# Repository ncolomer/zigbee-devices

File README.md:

# Zigbee Devices

DIY Zigbee firmware projects for the [Seeed Studio XIAO ESP32C6](https://wiki.seeedstudio.com/xiao_esp32c6_zigbee_arduino/), built with PlatformIO and the Arduino 3 framework. All devices join a [Zigbee2MQTT](https://www.zigbee2mqtt.io/) network.

## Projects

| Project | Description | Latest release |
|---|---|---|
| `garage-console` | 16-input switch console (Zigbee toggle/on-off sources) |  |
| `garage-doors` | 4-relay switch controller for garage and yard doors/gates |  |
| `garage-water` | Rain/grid water source selector + dual water meter |  |
| `garage-water-tank` | Ultrasonic water tank level monitor (OLED + Zigbee) |  |
| `water-meter` | Battery-powered pulse counter for mechanical water meters |  |

## Hardware

- **Board**: Seeed Studio XIAO ESP32C6
- **Build tool**: PlatformIO
- **Platform**: [pioarduino/platform-espressif32](https://github.com/pioarduino/platform-espressif32)

## Build

```bash
pio run -e debug    # debug build
pio run -e release  # release build
pio run --target upload  # flash firmware
```

## Release

Each firmware is released on its own, by pushing a `<project>-v<MAJOR.MINOR.PATCH>` tag:

```bash
git tag garage-doors-v0.1.2 && git push origin garage-doors-v0.1.2
```

[`release.yml`](.github/workflows/release.yml) builds the `release` env with that version and publishes a GitHub release with
the application image, the full flash image (`.factory.bin`), the Zigbee2MQTT external converter and, for OTA-enabled firmwares,
the Zigbee OTA image (`.ota`).
Local builds are versioned `0.0.0` unless `FIRMWARE_VERSION` is set.

Each release also refreshes the rolling `ota-index` release: its `index.json` lists the latest `.ota` of every firmware, for
Zigbee2MQTT's `ota.zigbee_ota_override_index_location`.

Firmwares opt into OTA with `custom_ota_manufacturer` and `custom_ota_image_type` (unique per firmware) in `platformio.ini`: the
firmware gets them as defines ([`scripts/firmware_version.py`](scripts/firmware_version.py)), and the workflow wraps the build into a
`.ota` with Espressif's [`image_builder_tool.py`](https://github.com/espressif/esp-zigbee-sdk/tree/master/tools/image_builder_tool).

## Structure

Each project follows this layout:

```
project/
├── platformio.ini
├── src/main.cpp
└── z2m-external-converter/   # Zigbee2MQTT external converter (if needed)
```

## Libraries

Shared code lives in `libraries/` and is referenced by projects via `lib_extra_dirs`.

## Serial Monitor

```zsh
espmon() { local p=$1 b=${2:-115200}; while :; do [[ -e $p ]] && { stty -f "$p" "$b" raw && cat "$p"; } || sleep .1; done }
espmon /dev/cu.usbmodem1101
```

Reconnects automatically when the device is unplugged/replugged.

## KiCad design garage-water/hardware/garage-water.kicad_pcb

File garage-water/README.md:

# Garage Water

Mains-powered Zigbee **router** for a garage water console. Drop-in replacement for a
ptvo.info `garage.water` firmware, reimplemented on a Seeed XIAO ESP32-C6 with a Grove
Shield. It selects the water source with a relay and totals two water meters.

## Hardware

- **Board**: Seeed Studio XIAO ESP32C6 + Grove Shield for XIAO
- **Power**: mains via USB-C (no battery) — always awake, no deep sleep
- **Relay**: 3.3V-piloted, Normally Open, **energized on LOW**

### Pin Connections

| Function            | Pin  | GPIO   | Notes                                              |
|---------------------|------|--------|----------------------------------------------------|
| Relay control       | D4   | 22     | ON/tank = HIGH (de-energized), OFF/grid = LOW      |
| Water meter 1 pulse | D1   | 1      | internal pull-up, FALLING interrupt, 10 ms debounce|
| Water meter 2 pulse | D2   | 2      | internal pull-up, FALLING interrupt, 10 ms debounce|
| Factory reset       | BOOT | 9      | onboard button, hold 3 s                           |
| Status LED          | —    | 15     | pairing / activity feedback                        |
| Spare               | D0, D7 | 0, 17 | unused                                            |

**Water source / fail-safe:** the relay idles HIGH (de-energized) via pull-up, and the
tank is wired to the de-energized side, so an **unpowered device selects the rain tank**.
Selecting grid (`OFF`) energizes the coil. Relay state is remembered across power loss.

## Behavior

- **Relay (EP1)**: Z2M on/off toggles the water source. `ON` = rain tank, `OFF` = grid.
  State persists to NVS and is restored (driven to the GPIO) on boot; a fresh device
  defaults to tank.
- **Water meters (EP2, EP3)**: each pulse adds `liters_per_pulse` to that meter's
  cumulative volume and reports it over the SE Metering cluster (`currentSummDelivered`).
- **Factory reset**: hold BOOT ≥ 3 s to leave the Zigbee network and re-pair. Meter
  totals and relay state (NVS) are preserved; a full wipe is `pio run --target erase`.

## Configuration

All configuration is done over Zigbee2MQTT after pairing:

| Entity                     | Description                                | Default |
|----------------------------|--------------------------------------------|---------|
| `state_relay`              | Water source (ON = tank, OFF = grid)       | tank    |
| `water_volume_meter1/2`    | Cumulative volume (m³, writable to calibrate) | 0    |
| `liters_per_pulse_meter1/2`| Liters per pulse (1–1000)                  | 10      |

## Storage (NVS)

- Relay state saved on every change.
- Each meter reading saved every 1000 L (1 m³) change, and immediately on a remote
  calibration write.

## Zigbee2MQTT

External converter in `z2m-external-converter/garage-water.mjs`:

1. Copy to `data/external_converters/`
2. Add to `configuration.yaml`:
   ```yaml
   external_converters:
     - garage-water.mjs
   ```
3. Restart Zigbee2MQTT

## Router mode

This firmware runs as a Zigbee **router** (`ZIGBEE_MODE_ZCZR`, `zigbee_zczr.csv`
partitions). Being permanently powered, it repeats the mesh and can parent other end
devices.

## OTA

Not implemented yet. The `zigbee_zczr.csv` partition scheme already provides the dual
OTA app slots, so OTA can be added later without repartitioning.

## Libraries

- `ZigbeeRelaySwitch` — genOnOff relay endpoint (toggle mode, NVS-persisted state)
- `ZigbeeWaterMeter` — SE Metering endpoint with custom `liters_per_pulse` attribute
- `StatusLed` — async LED blink via FreeRTOS task
- `Debug` — conditional serial logging (debug builds only)

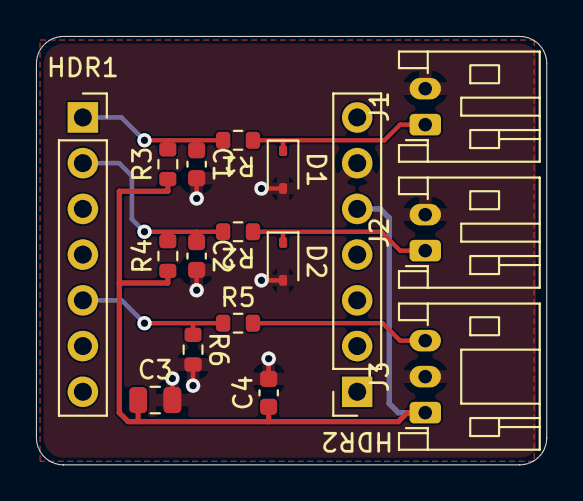
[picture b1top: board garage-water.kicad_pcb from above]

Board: 2 copper layers, 28.4 x 23.8 mm, 17 parts (0 on the bottom side), 8 nets.

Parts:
C1, C2, C4: 100nF; C_0603_1608Metric
C3: 10uF; C_0805_2012Metric
D1, D2: ESD 3.3V; D_SOD-323
HDR1, HDR2: Header_1x7_2.54mm; PinSocket_1x07_P2.54mm_Vertical
J1: METER1; JST_PH_S2B-PH-K_1x02_P2.00mm_Horizontal
J2: METER2; JST_PH_S2B-PH-K_1x02_P2.00mm_Horizontal
J3: RELAY; JST_PH_S3B-PH-K_1x03_P2.00mm_Horizontal
R1, R2: 1k; R_0603_1608Metric
R3, R4, R6: 10k; R_0603_1608Metric
R5: 330; R_0603_1608Metric

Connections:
/+3V3: C3.1, C4.1, HDR2.5, J3.1, R3.1, R4.1
/GND: C1.2, C2.2, C3.2, C4.2, D1.2, D2.2, HDR2.6, J1.2, J2.2, J3.2, R6.2
/M1_IN: D1.1, J1.1, R1.1
/M2_IN: D2.1, J2.1, R2.1
/METER1: C1.1, HDR1.1, R1.2, R3.2
/METER2: C2.1, HDR1.2, R2.2, R4.2
/RELAY_CMD: HDR1.5, R5.1, R6.1
/RELAY_IN: J3.3, R5.2

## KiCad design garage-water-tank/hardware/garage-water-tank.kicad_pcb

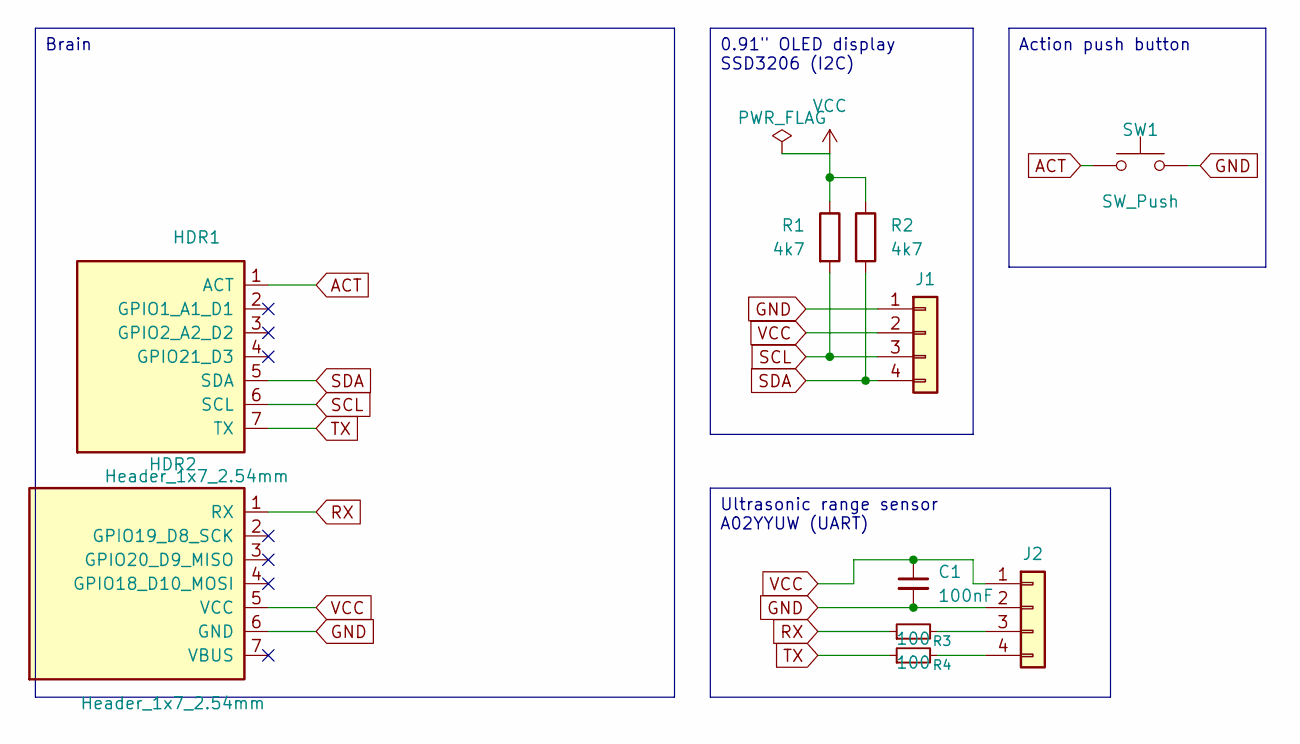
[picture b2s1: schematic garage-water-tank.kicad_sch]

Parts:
C1: 100nF; C_0805_2012Metric; LCSC C49678
HDR1, HDR2: Header_1x7_2.54mm; PinSocket_1x07_P2.54mm_Vertical; LCSC C22438157
J1: Conn_01x04; PinSocket_1x04_P2.54mm_Vertical_SMD_low_profile_Pin1Left; MPN HX PM2.54-1x4P TP-YQ; LCSC C42379197
J2: Conn_01x04; JST_PH_B4B-PH-K_1x04_P2.00mm_Vertical; MPN B4B-PH-K-S(LF)(SN); LCSC C131334
R1, R2: 4k7; R_0805_2012Metric; LCSC C17673
R3, R4: 100; R_0805_2012Metric; LCSC C17408
SW1: SW_Push; SW_PUSH_6mm_H13mm

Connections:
ACT: HDR1.1 (ACT), SW1.1
GND: C1.2, HDR2.6 (GND), J1.1, J2.2, SW1.2
unnamed: J2.3, R3.2
unnamed: J2.4, R4.2
RX: HDR2.1 (RX), R3.1
SCL: HDR1.6 (SCL), J1.3, R1.2
SDA: HDR1.5 (SDA), J1.4, R2.2
TX: HDR1.7 (TX), R4.1
VCC: C1.1, HDR2.5 (VCC), J1.2, J2.1, R1.1, R2.1

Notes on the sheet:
0.91" OLED display SSD3206 (I2C)
Ultrasonic range sensor A02YYUW (UART)
Action push button
Brain

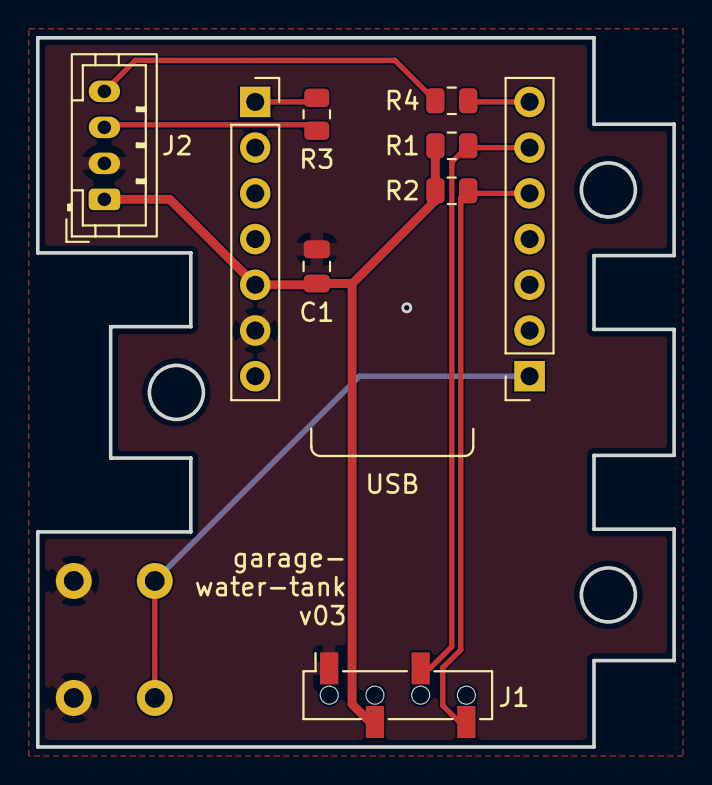
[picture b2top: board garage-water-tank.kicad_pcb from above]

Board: 2 copper layers, 35.3 x 39.4 mm, 10 parts (1 on the bottom side), 9 nets.

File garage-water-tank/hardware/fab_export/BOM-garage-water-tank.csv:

"Designator","Comment","Footprint","LCSC Part #"
"C1","100nF","Capacitor_SMD:C_0805_2012Metric","C49678"
"HDR1,HDR2","Header_1x7_2.54mm","Connector_PinSocket_2.54mm:PinSocket_1x07_P2.54mm_Vertical","C22438157"
"J1","Conn_01x04","garage-water-tank:PinSocket_1x04_P2.54mm_Vertical_SMD_low_profile_Pin1Left","C42379197"
"J2","Conn_01x04","Connector_JST:JST_PH_B4B-PH-K_1x04_P2.00mm_Vertical","C131334"
"R1,R2","4k7","Resistor_SMD:R_0805_2012Metric","C17673"
"R3,R4","100","Resistor_SMD:R_0805_2012Metric","C17408"

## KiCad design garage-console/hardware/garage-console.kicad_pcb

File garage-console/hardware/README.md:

# garage-console — hardware

16-channel switch input carrier board for a Seeed Studio XIAO ESP32C6.

Each of the 16 JST XH connectors carries GND plus one dedicated input, so a
momentary or toggle switch can be wired to it with a 2-wire cable. The ESP32C6
does not have 16 spare GPIOs, so the inputs land on an I²C port expander and the
expander raises an interrupt line when any of them changes.

Layout is modelled on the [Grove Shield for Seeeduino XIAO](https://wiki.seeedstudio.com/Grove-Shield-for-Seeeduino-XIAO-embedded-battery-management-chip/)
— a XIAO carrier with connectors broken out — minus the battery management, since
this board is permanently powered from the XIAO's USB-C.

## Design decisions

**PCF8575 rather than MCP23017.** The MCP23017 was the first choice, but its
GPA7 and GPB7 pins are output-only ([datasheet DS20001952D](https://ww1.microchip.com/downloads/en/DeviceDoc/20001952C.pdf),
pin table p.11), leaving only 14 usable inputs for 16 switches. The PCF8575 has
16 true quasi-bidirectional I/Os plus an open-drain interrupt output, so all 16
channels stay uniform. No local copy of the MCP23017 datasheet is kept — it's
a rejected alternative, not a part this design uses.

**No external pull-ups on the inputs.** The PCF8575 sources IOH = 30–300 µA to
VCC on any pin written high, which is the input configuration ([PCF8575 SCPS121I](datasheets/PCF8575-TI-datasheet.pdf)
§8.3). One 100 nF cap per input filters EMI picked up on the switch cabling and
debounces the contact in hardware. The trade-off is a slow release edge —
100 nF / 30 µA ≈ 8 ms worst case — which is harmless for switches and is why no
external pull-ups are fitted.

**Powered from the XIAO's USB-C.** +3V3 for the expander comes from the XIAO's
on-module LDO (module pin 12). Nothing on this board draws meaningful current
(PCF8575 standby is 10 µA max), so there is no regulator, no battery, and no
charger. No power indicator either — the XIAO's own `LED_BUILTIN` serves that
purpose, so the board carries no LED of its own.

## Files

| Path | Contents |
|---|---|
| `garage-console.kicad_pro` | KiCad project |
| `garage-console.kicad_sch` | Schematic (A3) |
| `garage-console.kicad_pcb` | Board layout |
| `datasheets/` | Local copies of every datasheet the design relies on |
| `3dmodels/` | Project-local STEP model(s) not available in any installed library |
| `garage_console.kicad_sym` | Project-local symbol library — `XIAO_HDR_A`/`XIAO_HDR_B`, the named-pin schematic symbols behind HDR1/HDR2 |
| `fab_export/` | Upload-ready production files, see Ordering |
| `jlcpcb-cpl-corrections.json` | Placement corrections applied to the CPL, see Ordering |

## Ordering

The three files in `fab_export/` are tracked, so the board can be ordered from
a clone without installing KiCad. On JLCPCB, upload:

| File | Where |
| --- | --- |
| `garage-console-gerbers.zip` | PCB order (Gerber) |
| `BOM-garage-console.csv` | Assembly → "BOM File" |
| `CPL-garage-console.csv` | Assembly → "CPL File" |

Economic PCBA, top side only, 2 layers. Economic supports through-hole, so the
JST connectors and both pin sockets are machine-placed along with the SMD parts;
nothing here needs hand-soldering. Everything on this board clears the Economic
limits comfortably — the tightest is U1's 0.65 mm pin pitch against a 0.4 mm
floor. Note the board is 21 mm wide, below Standard PCBA's 70 × 70 mm minimum,
so Economic is the only tier it fits.

To regenerate, pass the corrections file, or the placement corrections are lost:

```
export_manufacturing_package(
  fab_house="jlcpcb",
  jlcpcb_cpl_corrections_path=".../jlcpcb-cpl-corrections.json",
  ...)
```

**Always check JLCPCB's Component Placements preview before paying.** KiCad and
JLCPCB disagree about a package's zero-degree orientation, and Konnect's CPL
writes the KiCad footprint *anchor* into the `Mid X`/`Mid Y` columns instead of
the component midpoint ([Konnect #667](https://github.com/mixelpixx/Konnect/issues/667)),
which displaces anything anchored on pin 1. `jlcpcb-cpl-corrections.json`
compensates for both — rotations for the JSTs, U1 and the sockets, positions for
the JSTs and sockets — with every value verified in that preview. U1 needs no
position offset because the SSOP-24 anchor is already its centre. **Drop the
position offsets if #667 is fixed**, or they will double-correct.

Libraries: every footprint comes from a stock KiCad library, so `fp-lib-table`
registers nothing project-scope and is empty. The only project-local library is
`garage_console.kicad_sym`, registered in `sym-lib-table` under the
`garage_console` nickname. Nothing on the board comes from the
[Seeed OPL KiCad library](https://github.com/Seeed-Studio/OPL_Kicad_Library)
any more — it was only ever needed for the XIAO module's footprint, which this
design dropped (see Layout), so its entry was removed rather than left pointing
at a machine-specific absolute path that wouldn't resolve on anyone else's
clone. An empty `garage_console.pretty/` was dropped for the same reason: git
doesn't track empty directories, so registering one only guarantees a
missing-library path on a fresh clone. Re-add both the directory and its
`fp-lib-table` entry if a project-local footprint is ever needed.

## Switch channel map

`SWn` is pulled low while the switch on `Jn` is closed.

| Connector | Net | PCF8575 pin | Port bit |
|---|---|---|---|
| J1 | SW1 | 4 (P00) | port 0, bit 0 |
| J2 | SW2 | 5 (P01) | port 0, bit 1 |
| J3 | SW3 | 6 (P02) | port 0, bit 2 |
| J4 | SW4 | 7 (P03) | port 0, bit 3 |
| J5 | SW5 | 8 (P04) | port 0, bit 4 |
| J6 | SW6 | 9 (P05) | port 0, bit 5 |
| J7 | SW7 | 10 (P06) | port 0, bit 6 |
| J8 | SW8 | 11 (P07) | port 0, bit 7 |
| J9 | SW9 | 13 (P10) | port 1, bit 0 |
| J10 | SW10 | 14 (P11) | port 1, bit 1 |
| J11 | SW11 | 15 (P12) | port 1, bit 2 |
| J12 | SW12 | 16 (P13) | port 1, bit 3 |
| J13 | SW13 | 17 (P14) | port 1, bit 4 |
| J14 | SW14 | 18 (P15) | port 1, bit 5 |
| J15 | SW15 | 19 (P16) | port 1, bit 6 |
| J16 | SW16 | 20 (P17) | port 1, bit 7 |

Every connector's pin 2 is GND.

## XIAO interface

| XIAO pin | Signal | GPIO | Notes |
|---|---|---|---|
| 3 (D2) | PCF_INT | GPIO2 | active-low, open-drain, 10 k pull-up (R3) |
| 5 (D4) | SDA | GPIO22 | 4.7 k pull-up (R1) |
| 6 (D5) | SCL | GPIO23 | 4.7 k pull-up (R2) |
| 12 | +3V3 | — | board supply, from the XIAO LDO |
| 13 | GND | — | |

D0, D1, D3, D6–D10 and VBUS are unconnected — the expander covers all 16
channels, so no direct GPIOs are needed.

## Firmware notes

I²C address is **0x20** (7-bit): A2:A1:A0 are tied to GND, and the PCF8575
address is `0100 A2 A1 A0` (SCPS121I §8.3.3).

The part has no configuration or status registers. Writing `0xFFFF` once *is*
the input configuration; after that, reads return the pin states.

```cpp
Wire.begin(22, 23);                  // SDA=GPIO22 (D4), SCL=GPIO23 (D5)

Wire.beginTransmission(0x20);        // all 16 pins to input (weak pull-up on)
Wire.write(0xFF); Wire.write(0xFF);
Wire.endTransmission();

pinMode(2, INPUT);                   // R3 already pulls PCF_INT up
attachInterrupt(2, onChange, FALLING);

// in the handler's deferred work:
Wire.requestFrom(0x20, 2);
uint8_t p0 = Wire.read();            // SW1..SW8,  bit 0 = SW1
uint8_t p1 = Wire.read();            // SW9..SW16, bit 0 = SW9
// bit low = switch closed; the read also clears INT
```

Reading the port is what clears INT, so the read must happen on every interrupt
or the line stays asserted. A change arriving during the ACK pulse can be lost
(SCPS121I §8.3.2) — poll once per second alongside the interrupt so a missed edge
self-corrects.

## BOM

| Ref | Qty | Value | Footprint | LCSC | Notes |
|---|---|---|---|---|---|
| U1 | 1 | PCF8575 | SSOP-24 0.65 mm | [C2863388](https://www.lcsc.com/product-detail/C2863388.html) | TI PCF8575DBR |
| HDR1, HDR2 | 2 | Socket, 1×7, 2.54 mm | `PinSocket_1x07_P2.54mm_Vertical` | [C22438157](https://www.lcsc.com/product-detail/C22438157.html) | hanxia HX PM2.54-1x7P ZC-Y, female, 8.5 mm socket height; carry the XIAO module's real electrical connections, see Layout |
| J1–J16 | 16 | JST XH 2-pin | B2B-XH-A vertical, 2.5 mm | [C158012](https://www.lcsc.com/product-detail/C158012.html) | cable side: XHP-2 housing + SXH-001T-P0.6 crimps |
| C1 | 1 | 100 nF X7R | 0805 | [C49678](https://www.lcsc.com/product-detail/C49678.html) | U1 decoupling |
| C2 | 1 | 10 µF X5R | 0805 | [C15850](https://www.lcsc.com/product-detail/C15850.html) | +3V3 bulk, next to the module's supply pin (HDR2) |
| C3–C18 | 16 | 100 nF X7R | 0805 | [C49678](https://www.lcsc.com/product-detail/C49678.html) | input filter, one per channel |
| R1, R2 | 2 | 4.7 kΩ | 0805 | [C17673](https://www.lcsc.com/product-detail/C17673.html) | I²C pull-ups (the XIAO has none) |
| R3 | 1 | 10 kΩ | 0805 | [C17414](https://www.lcsc.com/product-detail/C17414.html) | PCF_INT pull-up |

**The Seeed Studio XIAO ESP32C6 module itself is not in this BOM or schematic at all** — it
carries no copper on this board (see Layout) and its own pinout isn't formally
documented anywhere in this design beyond HDR1/HDR2's own pin names, so it's
easy to read the BOM and schematic and not realize a module is needed at all.
It must be sourced separately (Seeed 113991054), and its own DIP-14
through-holes need a set of male 2.54 mm pins soldered in by hand — these
plug into HDR1/HDR2's sockets, which is how the module is mounted.

No mounting holes — this board lives inside an enclosure that doesn't need them.

All passive LCSC numbers are JLCPCB Basic-library parts (no Extended-part assembly fee), picked for highest stock among matching value/footprint/tolerance. U1, J1–J16, and HDR1/HDR2 have no Basic-library equivalent — this specific I/O expander, the JST connectors, and 2.54 mm pin sockets aren't stocked there — so each lists the highest-stock Extended part matching the MPN already in the schematic.

Every part above also carries its LCSC number as an `LCSC` field on the schematic symbol itself (not just this table), so it flows straight through KiCad's own BOM export and into `kicad-jlcpcb-tools`.

Fab target: JLCPCB, 2 layer, 0.2 mm minimum trace and clearance. All passives are
0805 — easier to hand-solder/rework than 0402, at the cost of a slightly larger
board.

## Layout

The board is a 169.3 × 21.2 mm horizontal strip (trimmed to the connectors'
and module's actual extents — no unused margin, since there are no mounting
holes to clear). The top and bottom edges are colinear with the module's real
body (its footprint's `F.Courtyard`/`F.Fab` outline, back when it still had a
dedicated footprint — not the USB-C connector's silkscreen mark, which is
meant to hang off the edge — see below), not just "close to it". The left and
right edges are mirrored around the connector block's own centerline
(x = 93.15 mm) rather than the board's raw geometric center, which an earlier
revision's asymmetric width trim had drifted 0.75 mm away from. The 16 JST
connectors form two rows of 8 (one row per board edge), split into two
4-connector blocks per row with U1/HDR1/HDR2 sitting in the gap between the
blocks, centered both horizontally and vertically. The module's ceramic
antenna faces the top edge (right at the board edge — see antenna clearance
note below), USB-C faces the bottom edge. Each filter cap (C3–C18) is rotated
90° from a naive placement so its short axis (1.25 mm) faces the tight
left-right direction between connector columns, trading it for the board's
more plentiful vertical room.

**Filter caps are genuinely mirror-symmetric block-to-block.** Every JST
footprint (rotation 0° in both blocks) extends 5.475 mm to its own right and
only 2.975 mm to its left — an asymmetry baked into the footprint itself that
doesn't flip between blocks, so a true mirror needs an *asymmetric* offset
magnitude, not just an opposite sign. Left-block caps (C3–C10) sit at
`connector_x + 7.75 mm` (the connector's long side, verified clear of its
own courtyard with margin); most right-block caps (C12–C14, C16–C18) sit at
`connector_x − 5.3 mm` — the connector's short side, which needs less
clearance than the long side does. **C11 and C15 are the two exceptions**:
both sit at `connector_x + 7.805 mm`, on the same side as the left-block
caps rather than mirrored, because the mirrored position would put them
inside the R1–R3 group's courtyards (R1–R3 are fixed, off-limits to move).

**The XIAO module has no schematic symbol and no PCB footprint at all.** Its
real electrical connections are carried entirely by two standard 1×7,
2.54 mm female sockets, HDR1 and HDR2 — one per physical pin column of the
module's DIP-14 footprint (HDR1: GPIO0/GPIO1/PCF_INT/GPIO21/SDA/SCL/GPIO16;
HDR2: GPIO17/GPIO19/GPIO20/GPIO18/+3V3/GND/VBUS), each with correctly-named
pins in the schematic. HDR1/HDR2 are soldered flat onto this board; the
module's own male pins (soldered into its DIP-14 holes by hand, off-board —
not a part in this BOM) plug into the sockets, physically elevating the
module above the board surface by the socket height so it clears U1 and C1
underneath without touching them. This keeps every component on one side of
the board, which JLCPCB only charges a single assembly fee for (a 2-sided
assembly would double that fee for the sake of two parts). With no PCB
footprint for the module at all, there's nothing for the `courtyards_overlap`
DRC check to compare against U1/C1's courtyards in the first place.

An earlier revision instead gave the module its own dedicated PCB footprint
— zero pads, no courtyard, existing purely to hold the 3D model — while
keeping its schematic symbol fully wired for documentation. That worked, but
KiCad's schematic-parity check expects every schematic pin to find a
correspondingly-numbered footprint pad, and a zero-pad footprint can never
satisfy that: it produced a structural, permanent warning for all 14 pins
("no pad found for pin N in schematic"), one that could only be silenced
with a DRC exclusion, not actually resolved. Since 3D models are attached to
footprints and never inspected by DRC/ERC at all, the cleaner fix was to drop
that placeholder symbol/footprint entirely and instead give HDR1's own real,
already-connected footprint a *second*, independent 3D model entry — the
module's STEP file, positioned via its own offset/rotation so it renders in
the same physical spot as before. No symbol means no parity check to fail;
the module still renders correctly in the 3D viewer since a footprint (HDR1's)
is still there to carry it. The final transform is offset (13.73, −9.36,
8.8 mm), rotation (−90°, 0°, −90°).

**HDR1/HDR2's spacing was wrong for a while, and so was the transform above
until it was corrected alongside it.** An earlier revision placed HDR1 and
HDR2 16.4925 mm apart — the real, authoritative spacing (confirmed from
Seeed's own official OPL KiCad library footprint,
`Seeed Studio XIAO Series Library/XIAO-ESP32-C6-DIP.kicad_mod`, the same
library this project's schematic uses) is 15.24 mm, centered on x = 93.15 mm.
The footprint defines each pin twice — a real `thru_hole circle` pad and a
cosmetic `smd roundrect` annular pad 0.835 mm further out — and the original
extraction picked up the cosmetic pad for HDR2 and an incorrect average of
both pads for HDR1, instead of the real through-holes alone. Corrected
positions: HDR1 x = 100.77 (was 101.1875), HDR2 x = 85.53 (was 84.695), Y and
rotation unchanged for both. The module's 3D-model offset above is the
result *after* this correction — HDR1 moving −0.4175 mm required the same
shift in the model's offset.x to keep the module's world-space position
exactly where it had been visually confirmed correct. Re-verified with
`get_board_2d_view` (not `kicad-cli pcb render` — the two don't visually
agree closely enough for fine placement checks, confirmed directly): the
module now sits flush against both header columns with no gap on either
side. The one caveat on the model itself is unchanged: this second model is
a board-instance-local addition, not part of HDR1's stock library footprint
(`Connector_PinSocket_2.54mm:PinSocket_1x07_P2.54mm_Vertical`) — running
"Update Footprint from Library" on HDR1 would silently drop it.

Swapping the module's oversized, module-specific pads for HDR1/HDR2's small
standard socket pads also freed real copper/routing room in what was the
densest spot on the board — those oversized pads were a direct cause of
several clearance fights during autorouting in earlier revisions.

**Antenna clearance.** No keepout zone under the module's antenna end — with the
antenna now at the board's physical edge (copper on one side only, not
surrounding it) and the module elevated a few mm above the board surface on
the headers, the RF justification for a precautionary carve-out is much
weaker than when the module sat flush on the surface. Removed rather than
carried forward as unnecessary caution.

**Ground plane.** Both copper layers carry a full-board GND pour with a
*solid* pad connection (no thermal-relief spokes) rather than KiCad's default
thermal mode. The PCF8575's 0.65 mm pin pitch is too tight for the standard
2-spoke thermal relief — it kept failing DRC's `starved_thermal` check — and
solid fill also avoids the connectivity islands thermal relief can leave
behind on a densely-routed 2-layer board. The pour outline sits 0.2 mm inside
the board edge on all sides — JLCPCB's published minimum copper-to-routed-edge
clearance — rather than the tighter, sub-minimum inset an earlier revision
used. No dedicated GND stitching vias are needed — the 16 JST connectors'
and both header sockets' through-hole pins already bridge F.Cu and B.Cu
everywhere the dense signal routing would otherwise leave a pour region
isolated; each fill fragment on both layers was checked directly against
the via/pad list and every one lands on a real GND connection.

One `unconnected_items` DRC finding is left and is a known, checked-benign
zone-fill artifact, not a real gap: at the top-right corner (the rounded
corner's zone-inset vertex, board edge minus the 3 mm corner radius) DRC
reports `GND_top_solid` and `GND_bottom_solid` as unconnected. Direct
polygon inspection shows both layers' fill share the exact same points at
that vertex, and both zones tie into the same net through dozens of shared
GND pads elsewhere on the board — a stitching via added right at the flagged
point didn't change the finding (and cost real edge clearance), confirming
it's a KiCad connectivity-check quirk specific to that corner geometry, not
an electrical break. This has now shown up at the same relative corner
across more than one revision of this outline.

**Routing.** Autorouted with [Freerouting](https://github.com/freerouting/freerouting)
via its MCP server, driven from a Specctra DSN exported through KiCad's own
`pcbnew.ExportSpecctraDSN`/`ImportSpecctraSES` (the same mechanism as *File →
Export/Import → Specctra*, just scripted). The GND pours export as Specctra
`plane` records **as long as they exist at export time** — Freerouting then
treats GND as already satisfied by the plane and never draws an explicit GND
trace or via for it, so the 16 filter caps' GND legs, and everything else on
the net, rely purely on the pour (see Ground Plane above). This is
different from the antenna keepout (removed in this revision) and any other
rule-area keepout zone, which Freerouting treats as a hard routing obstacle
rather than just a copper-fill exclusion — a keepout can only exist once
routing is done, while a GND *pour* zone should stay in place through export
precisely so Freerouting reads it as a plane instead of routing GND as
ordinary traces.
A few of Freerouting's automatic-neckdown segments came back under the 0.2 mm
fab minimum and were widened by hand after import; a couple of vias needed
small nudges to clear adjacent copper. One or two connections per revision
have consistently been too tightly boxed in for Freerouting to close on its
own — U1's SW-net pins sit on a 0.65 mm pitch with GND/SDA/SCL fan-out
immediately around them, and different specific connections have hit this
depending on the exact routing pass (this revision: `SW11` between C13 and
U1 pin 15, plus a trivial direct `+3V3` link between R1 and R2 that
Freerouting simply missed). Each SW-net case was solved with a small
grid-based pathfinder (clearance-aware, both copper layers, via cost
included) rather than by guesswork, since the pocket is tight enough that
hand-picked straight lines and even a first pathfinder pass (modeling only
trace clearance, not the larger clearance a via itself needs) reliably
landed on or too close to existing copper — the working version models via
placement with its own, stricter clearance check before committing to a
layer-switch point. Every change was re-verified with a fresh DRC pass.

**3D models.** J1–J16, U1, HDR1 and HDR2 use the standard `.step` models
bundled with their KiCad libraries. The OPL library's XIAO footprints have no
dedicated XIAO ESP32C6 model — only placeholder bodies for other XIAO
variants, gated behind a `${AMZPATH}` environment variable this machine
doesn't have configured — so `3dmodels/seeed-studio-xiao-esp32c6.step`
(copied from the `water-tank-monitor` project's assets) is used instead, via
a `${KIPRJMOD}`-relative path, attached as HDR1's second 3D model entry (see
Layout for why and the exact transform).

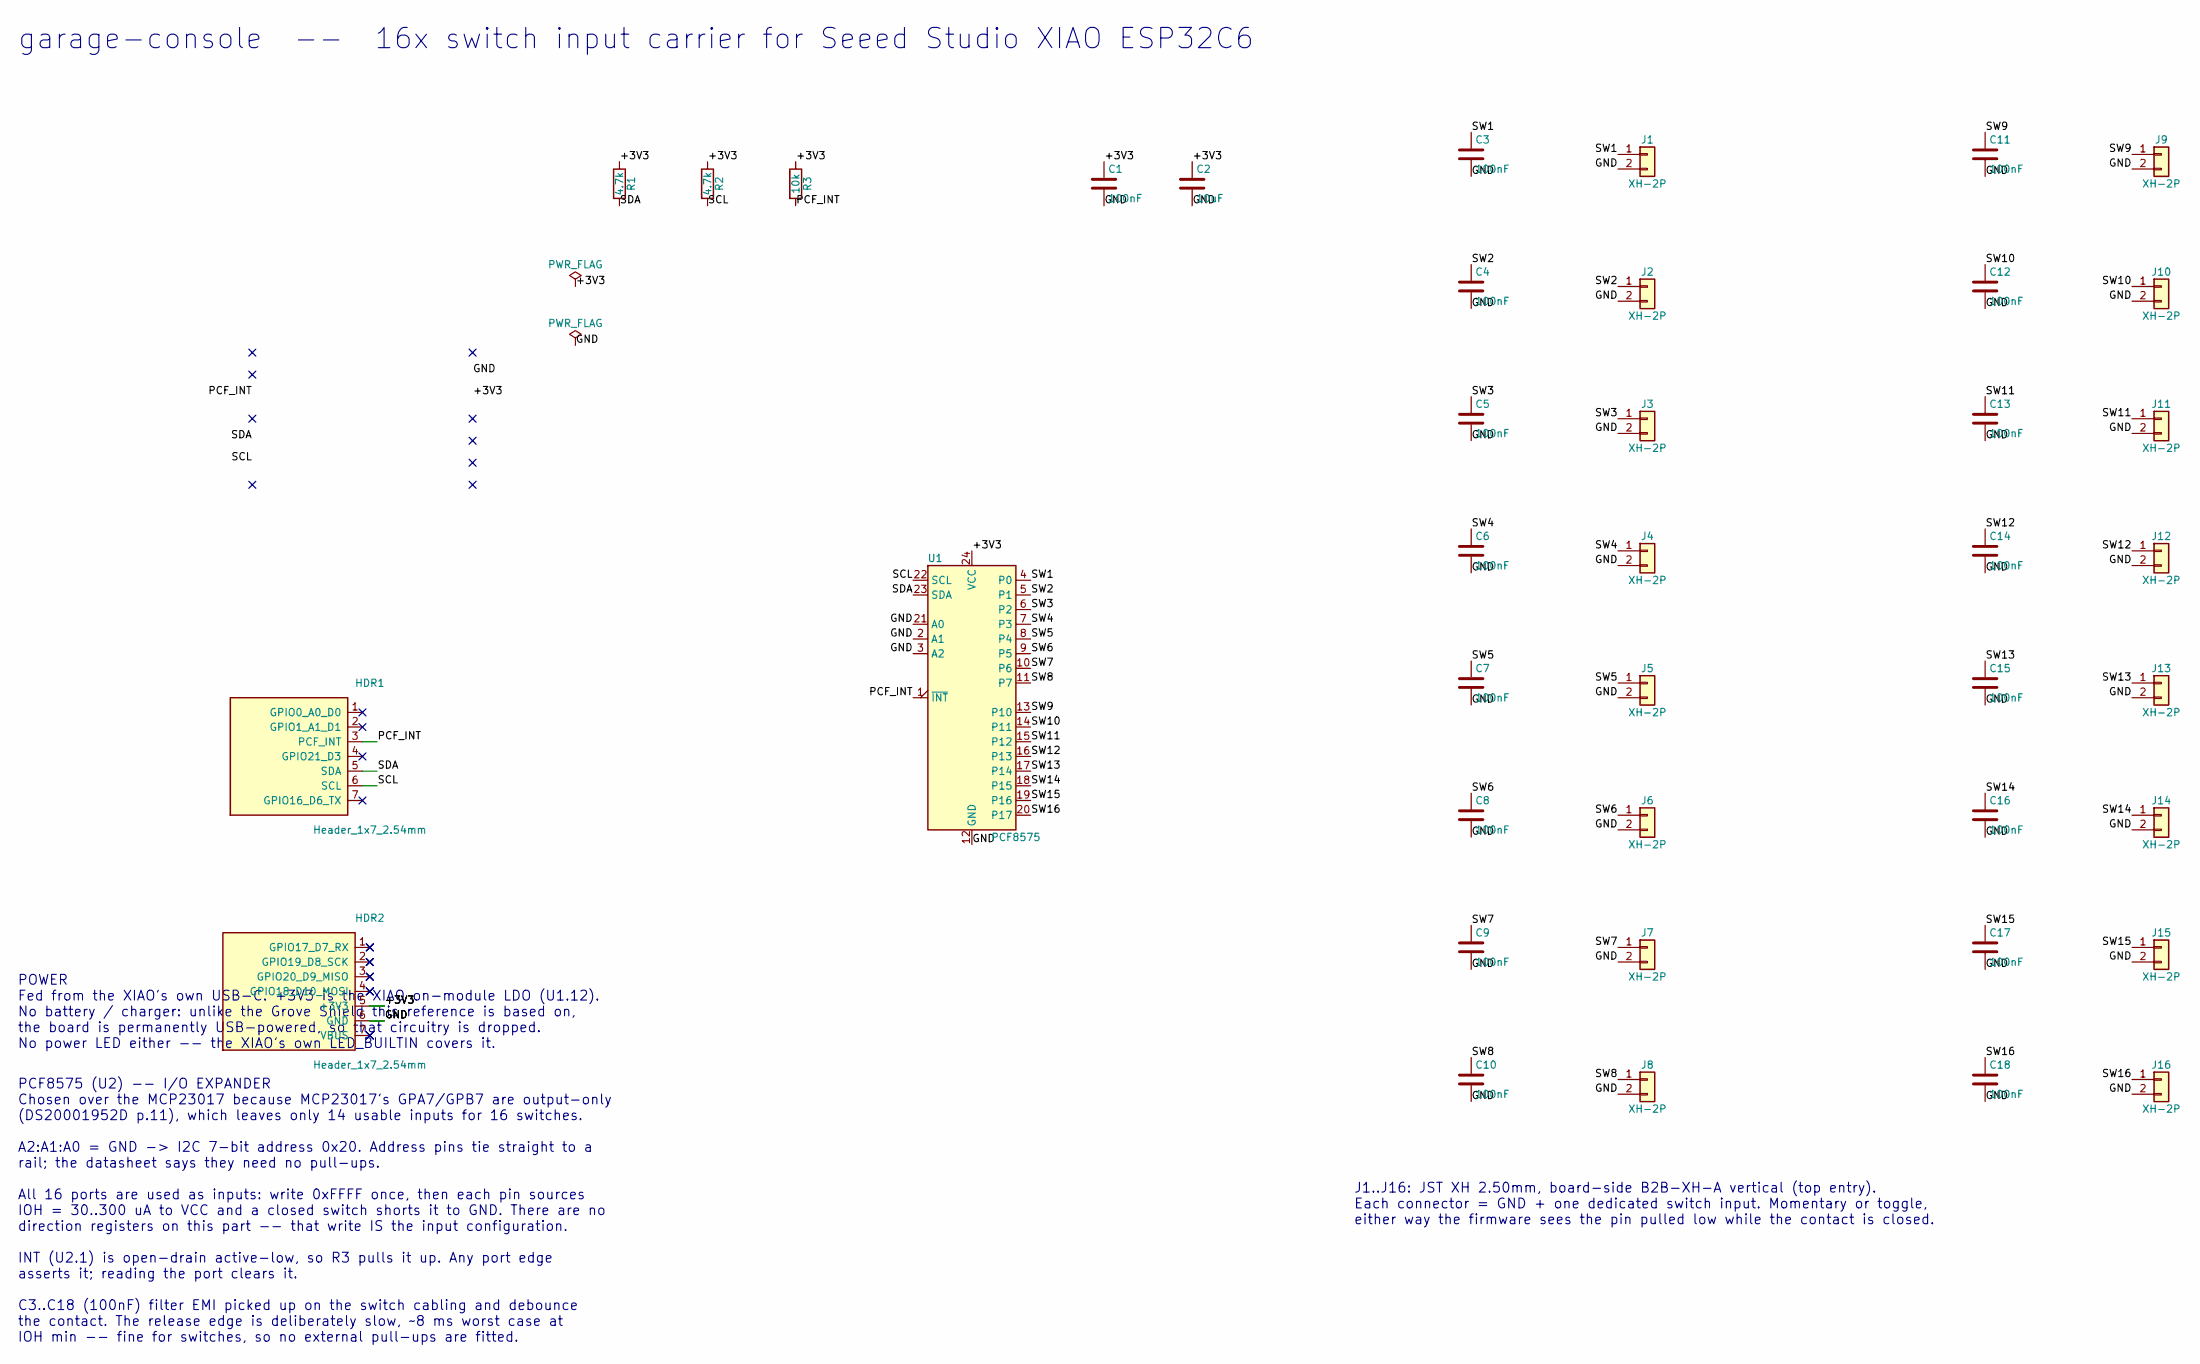
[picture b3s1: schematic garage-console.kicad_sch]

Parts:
C1, C3, C4, C5, C6, C7, C8, C9, C10, C11, C12, C13, C14, C15, C16, C17, C18: 100nF; C_0805_2012Metric; LCSC C49678
C2: 10uF; C_0805_2012Metric; LCSC C15850
HDR1, HDR2: Header_1x7_2.54mm; PinSocket_1x07_P2.54mm_Vertical; LCSC C22438157
J1, J2, J3, J4, J5, J6, J7, J8, J9, J10, J11, J12, J13, J14, J15, J16: XH-2P; JST_XH_B2B-XH-A_1x02_P2.50mm_Vertical; LCSC C158012
R1, R2: 4.7k; R_0805_2012Metric; LCSC C17673
R3: 10k; R_0805_2012Metric; LCSC C17414
U1: PCF8575; SSOP-24_5.3x8.2mm_P0.65mm; LCSC C2863388

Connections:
/+3V3: C1.1, C2.1, HDR2.5 (+3V3), R1.1, R2.1, R3.1, U1.24 (VCC)
/GND: C1.2, C2.2, C3.2, C4.2, C5.2, C6.2, C7.2, C8.2, C9.2, C10.2, C11.2, C12.2, C13.2, C14.2, C15.2, C16.2, C17.2, C18.2, HDR2.6 (GND), J1.2, J2.2, J3.2, J4.2, J5.2, J6.2, J7.2, J8.2, J9.2, J10.2, J11.2, J12.2, J13.2, J14.2, J15.2, J16.2, U1.2 (A1), U1.3 (A2), U1.12 (GND), U1.21 (A0)
/PCF_INT: HDR1.3 (PCF_INT), R3.2, U1.1 (~INT)
/SCL: HDR1.6 (SCL), R2.2, U1.22 (SCL)
/SDA: HDR1.5 (SDA), R1.2, U1.23 (SDA)
/SW1: C3.1, J1.1, U1.4 (P0)
/SW2: C4.1, J2.1, U1.5 (P1)
/SW3: C5.1, J3.1, U1.6 (P2)
/SW4: C6.1, J4.1, U1.7 (P3)
/SW5: C7.1, J5.1, U1.8 (P4)
/SW6: C8.1, J6.1, U1.9 (P5)
/SW7: C9.1, J7.1, U1.10 (P6)
/SW8: C10.1, J8.1, U1.11 (P7)
/SW9: C11.1, J9.1, U1.13 (P10)
/SW10: C12.1, J10.1, U1.14 (P11)
/SW11: C13.1, J11.1, U1.15 (P12)
/SW12: C14.1, J12.1, U1.16 (P13)
/SW13: C15.1, J13.1, U1.17 (P14)
/SW14: C16.1, J14.1, U1.18 (P15)
/SW15: C17.1, J15.1, U1.19 (P16)
/SW16: C18.1, J16.1, U1.20 (P17)

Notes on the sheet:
garage-console -- 16x switch input carrier for Seeed Studio XIAO ESP32C6
J1..J16: JST XH 2.50mm, board-side B2B-XH-A vertical (top entry). Each connector = GND + one dedicated switch input. Momentary or toggle, either way the firmware sees the pin pulled low while the contact is closed.
PCF8575 (U2) -- I/O EXPANDER Chosen over the MCP23017 because MCP23017's GPA7/GPB7 are output-only (DS20001952D p.11), which leaves only 14 usable inputs for 16 switches. A2:A1:A0 = GND -> I2C 7-bit address 0x20. Address pins tie straight to a rail; the datasheet says they need no pull-ups. All 16 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
POWER Fed from the XIAO's own USB-C. +3V3 is the XIAO on-module LDO (U1.12). No battery / charger: unlike the Grove Shield this reference is based on, the board is permanently USB-powered, so that circuitry is dropped. No power LED either -- the XIAO's own LED_BUILTIN covers it.

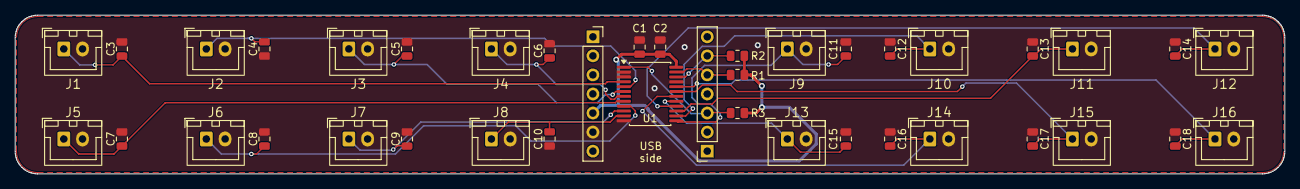
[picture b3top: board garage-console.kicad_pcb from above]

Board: 2 copper layers, 169.2 x 21.1 mm, 40 parts (0 on the bottom side), 21 nets.

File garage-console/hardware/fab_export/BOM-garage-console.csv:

"Designator","Comment","Footprint","LCSC Part #"
"C1,C3,C4,C5,C6,C7,C8,C9,C10,C11,C12,C13,C14,C15,C16,C17,C18","100nF","Capacitor_SMD:C_0805_2012Metric","C49678"
"C2","10uF","Capacitor_SMD:C_0805_2012Metric","C15850"
"HDR1,HDR2","Header_1x7_2.54mm","Connector_PinSocket_2.54mm:PinSocket_1x07_P2.54mm_Vertical","C22438157"
"J1,J2,J3,J4,J5,J6,J7,J8,J9,J10,J11,J12,J13,J14,J15,J16","XH-2P","Connector_JST:JST_XH_B2B-XH-A_1x02_P2.50mm_Vertical","C158012"
"R1,R2","4.7k","Resistor_SMD:R_0805_2012Metric","C17673"
"R3","10k","Resistor_SMD:R_0805_2012Metric","C17414"
"U1","PCF8575","Package_SO:SSOP-24_5.3x8.2mm_P0.65mm","C2863388"

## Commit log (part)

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2026-03-15 Initial commit
    Made-with: Cursor
2026-03-15 Add garage-doors project
    Includes firmware, Z2M external converter, and required shared libraries
    (ZigbeeRelaySwitch, StatusLed, Debug).
    Made-with: Cursor
2026-03-15 Add AGENTS.md with project conventions and patterns
    Made-with: Cursor
